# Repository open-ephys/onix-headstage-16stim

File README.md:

# ONIX 16-Channel Bidirectional Headstage
Serialized, multifunction headstage for wire electrode or silicon probe recordings.

- 16x bi-directional electrophysiology channels (±7V stimulus compliance)
- Integrated stimulus sequencer and memory
- Integrated real-time, room-scale 3D-position tracking
- Integrated absolute orientation tracking

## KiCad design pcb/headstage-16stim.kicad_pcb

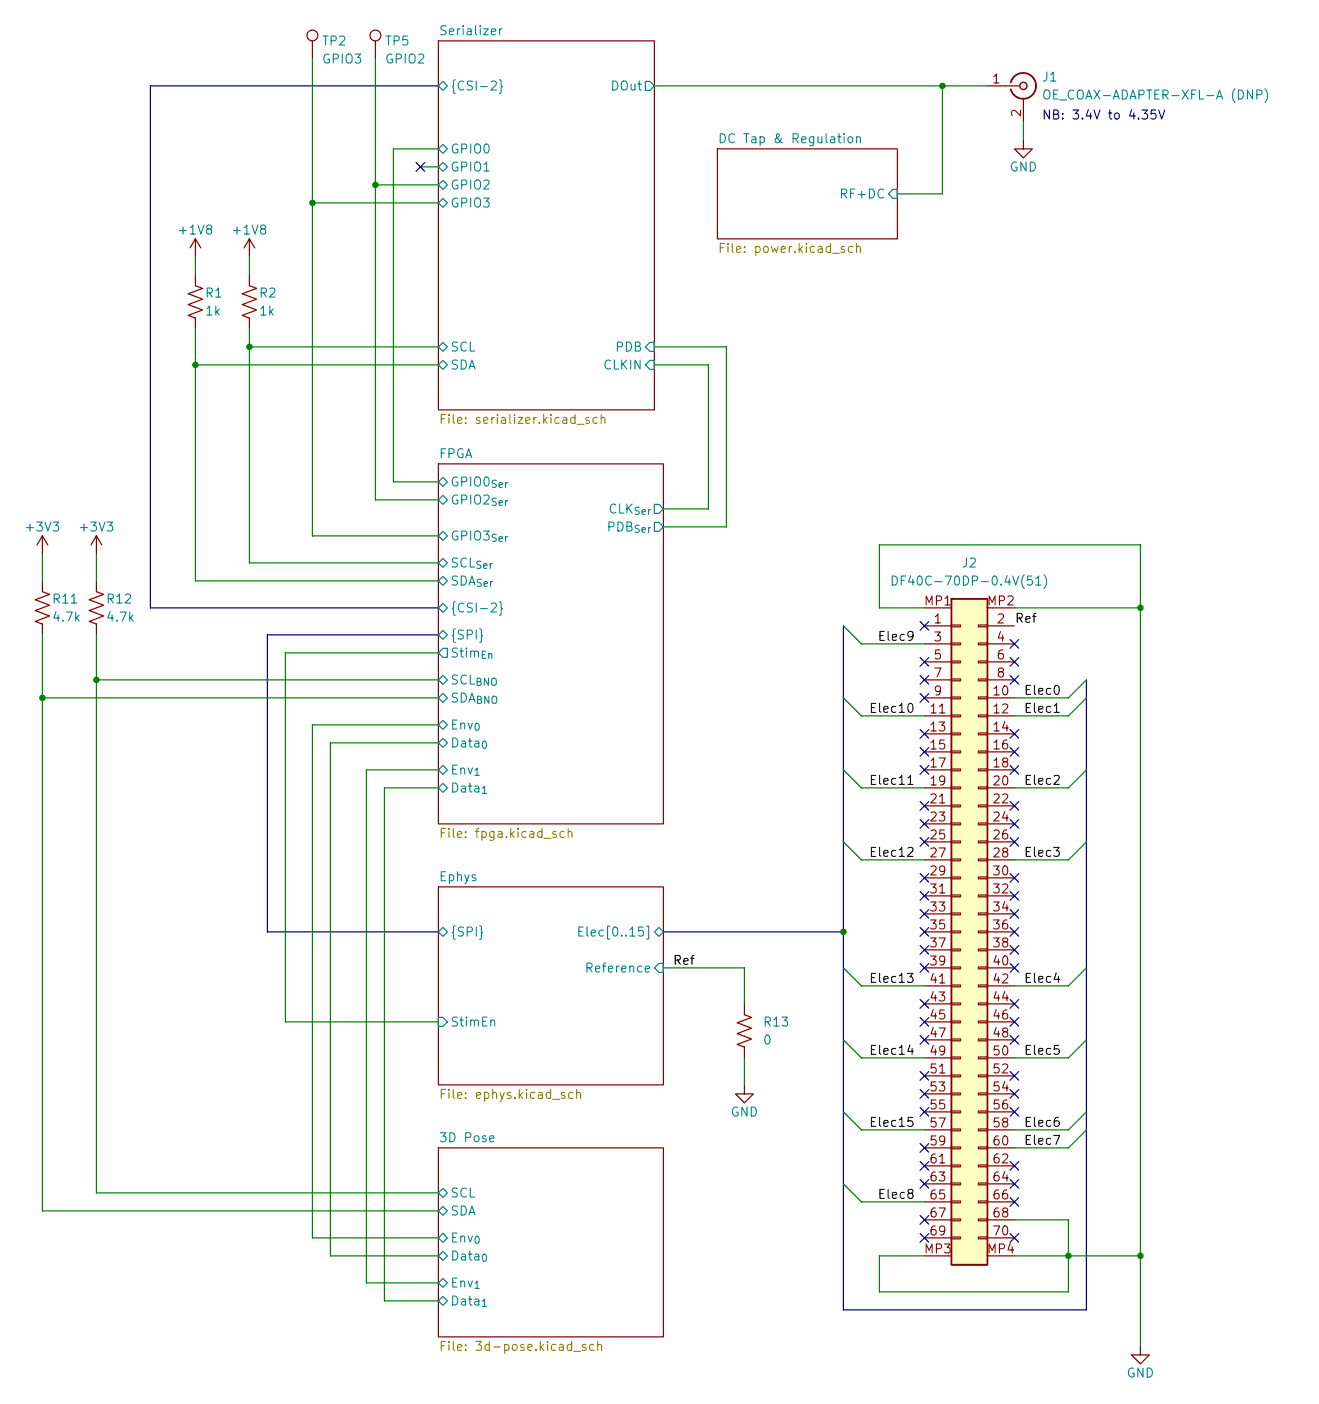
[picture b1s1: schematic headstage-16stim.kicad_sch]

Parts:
J1: OE_COAX-ADAPTER-XFL-A (DNP); OE_COAX-ADAPTER-XFL-A
J2: DF40C-70DP-0.4V(51); HIROSE_DF40C70DP04V51
R1, R2: 1k; R_0201_0603Metric
R11, R12: 4.7k; R_0201_0603Metric
R13: 0; R_0201_0603Metric
TP2: GPIO3; TestPoint_Pad_D0.6mm
TP5: GPIO2; TestPoint_Pad_D0.6mm

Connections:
+1V8: R1.1, R2.1; also elsewhere on the board
+3V3: R11.1, R12.1; also elsewhere on the board
/3D Pose/SCL: R12.2; also elsewhere on the board
/3D Pose/SDA: R11.2; also elsewhere on the board
/DC Tap & Regulation/RF+DC: J1.1 (In); also elsewhere on the board
/Ephys/Elec0: J2.10; also elsewhere on the board
/Ephys/Elec1: J2.12; also elsewhere on the board
/Ephys/Elec2: J2.20; also elsewhere on the board
/Ephys/Elec3: J2.28; also elsewhere on the board
/Ephys/Elec4: J2.42; also elsewhere on the board
/Ephys/Elec5: J2.50; also elsewhere on the board
/Ephys/Elec6: J2.58; also elsewhere on the board
/Ephys/Elec7: J2.60; also elsewhere on the board
/Ephys/Elec8: J2.65; also elsewhere on the board
/Ephys/Elec9: J2.3; also elsewhere on the board
/Ephys/Elec10: J2.11; also elsewhere on the board
/Ephys/Elec11: J2.19; also elsewhere on the board
/Ephys/Elec12: J2.27; also elsewhere on the board
/Ephys/Elec13: J2.41; also elsewhere on the board
/Ephys/Elec14: J2.49; also elsewhere on the board
/Ephys/Elec15: J2.57; also elsewhere on the board
/FPGA/GPIO2_{Ser}: TP5.1; also elsewhere on the board
/FPGA/GPIO3_{Ser}: TP2.1; also elsewhere on the board
/FPGA/SCL_{Ser}: R2.2; also elsewhere on the board
/FPGA/SDA_{Ser}: R1.2; also elsewhere on the board
/Ref: J2.2, R13.1; also elsewhere on the board
GND: J1.2 (Ext), J2.68, J2.MP1 (MountPin1), J2.MP2 (MountPin2), J2.MP3 (MountPin3), J2.MP4 (MountPin4), R13.2; also elsewhere on the board

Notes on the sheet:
NB: 3.4V to 4.35V

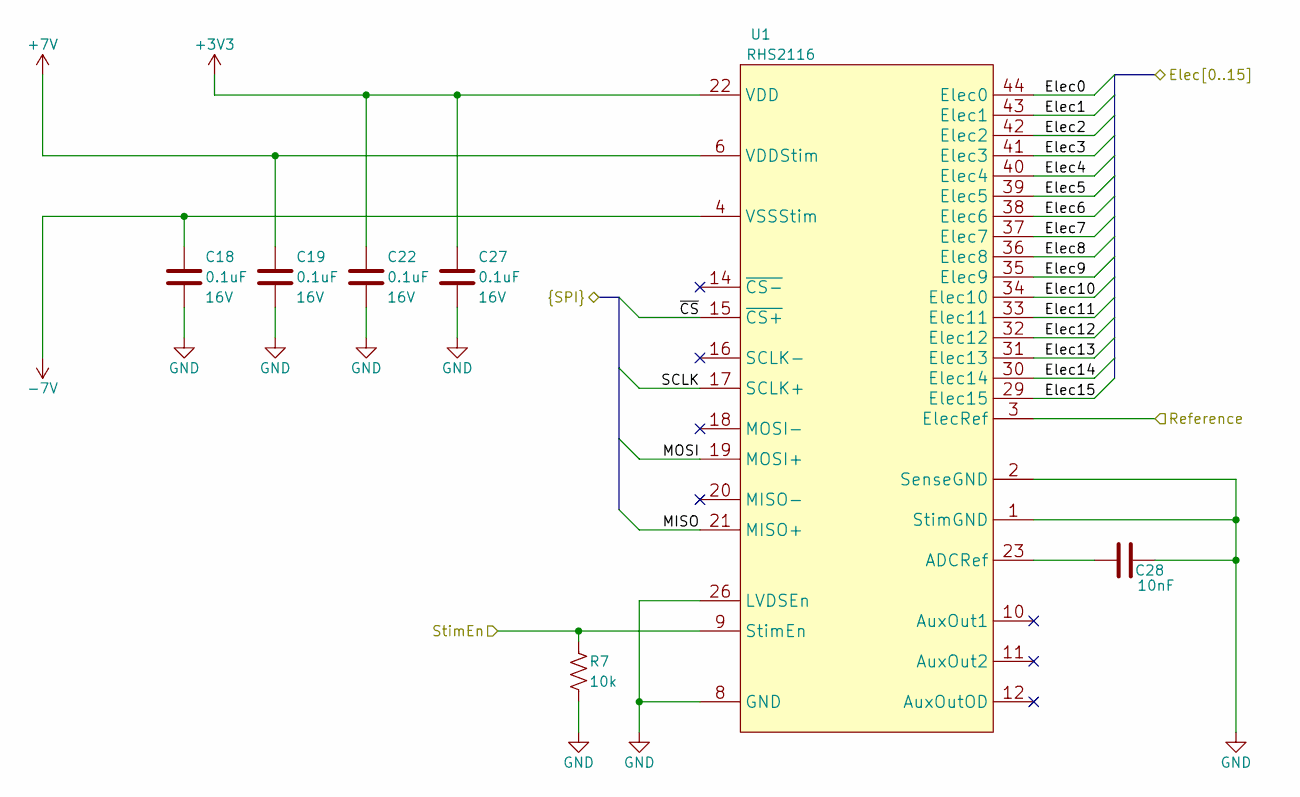
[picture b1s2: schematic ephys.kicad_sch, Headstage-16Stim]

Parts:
C18, C19, C22, C27: 0.1uF; C_0201_0603Metric; Voltage 16V
C28: 10nF; C_0201_0603Metric; Voltage 35V
R7: 10k; R_0201_0603Metric
U1: RHS2116; INTAN_QFN44-7.0x7.0x0.8_P0.5

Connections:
+3V3: C22.1, C27.1, U1.22 (VDD), U1.27 (VDD), U1.28 (VDD); also elsewhere on the board
+7V: C19.1, U1.6 (VDDStim), U1.7 (VDDStim); also elsewhere on the board
-7V: C18.1, U1.4 (VSSStim), U1.5 (VSSStim), U1.45 (VSSStim); also elsewhere on the board
/Ephys/Elec0: U1.44 (Elec0); also elsewhere on the board
/Ephys/Elec1: U1.43 (Elec1); also elsewhere on the board
/Ephys/Elec2: U1.42 (Elec2); also elsewhere on the board
/Ephys/Elec3: U1.41 (Elec3); also elsewhere on the board
/Ephys/Elec4: U1.40 (Elec4); also elsewhere on the board
/Ephys/Elec5: U1.39 (Elec5); also elsewhere on the board
/Ephys/Elec6: U1.38 (Elec6); also elsewhere on the board
/Ephys/Elec7: U1.37 (Elec7); also elsewhere on the board
/Ephys/Elec8: U1.36 (Elec8); also elsewhere on the board
/Ephys/Elec9: U1.35 (Elec9); also elsewhere on the board
/Ephys/Elec10: U1.34 (Elec10); also elsewhere on the board
/Ephys/Elec11: U1.33 (Elec11); also elsewhere on the board
/Ephys/Elec12: U1.32 (Elec12); also elsewhere on the board
/Ephys/Elec13: U1.31 (Elec13); also elsewhere on the board
/Ephys/Elec14: U1.30 (Elec14); also elsewhere on the board
/Ephys/Elec15: U1.29 (Elec15); also elsewhere on the board
/Ephys/MISO: U1.21 (MISO+); also elsewhere on the board
/Ephys/MOSI: U1.19 (MOSI+); also elsewhere on the board
/Ephys/SCLK: U1.17 (SCLK+); also elsewhere on the board
/Ephys/StimEn: R7.1, U1.9 (StimEn); also elsewhere on the board
/Ephys/~CS: U1.15 (~CS+); also elsewhere on the board
/Ref: U1.3 (ElecRef); also elsewhere on the board
GND: C18.2, C19.2, C22.2, C27.2, C28.2, R7.2, U1.1 (StimGND), U1.2 (SenseGND), U1.8 (GND), U1.13 (GND), U1.24 (GND), U1.25 (GND), U1.26 (LVDSEn); also elsewhere on the board
unnamed: C28.1, U1.23 (ADCRef)

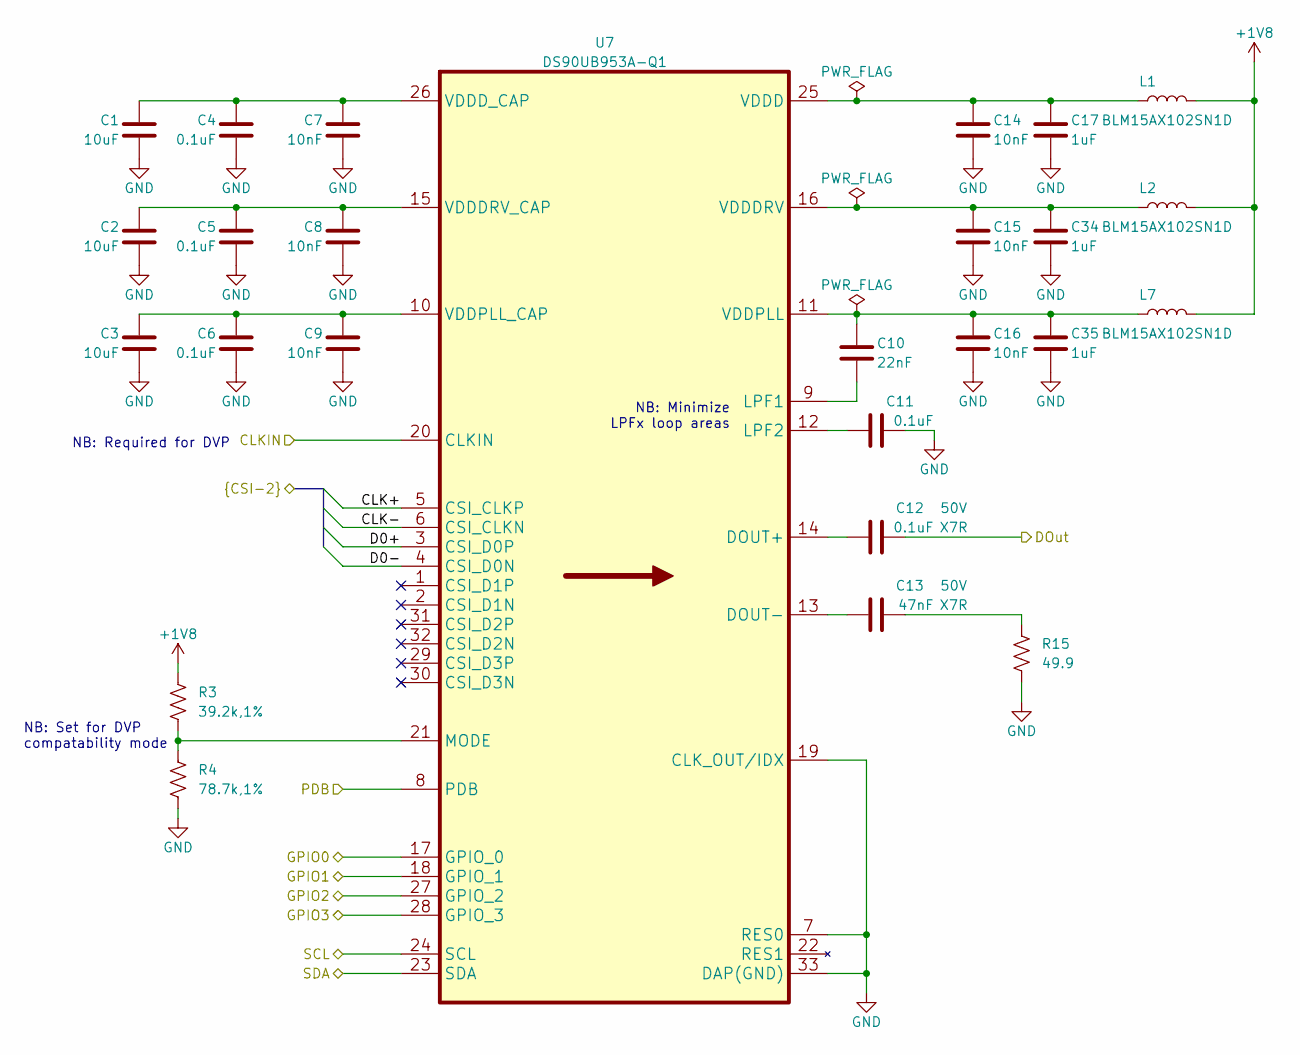
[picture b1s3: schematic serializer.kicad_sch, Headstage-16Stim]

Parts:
C1, C2, C3: 10uF; C_0402_1005Metric; Voltage 10V
C4, C5, C6, C11: 0.1uF; C_0201_0603Metric; Voltage 16V
C7, C8, C9, C14, C15, C16: 10nF; C_0201_0603Metric; Voltage 35V
C10: 22nF; C_0402_1005Metric; Voltage 35V
C12: 0.1uF; C_0402_1005Metric; Voltage 50V
C13: 47nF; C_0402_1005Metric; Voltage 50V
C17, C34, C35: 1uF; C_0402_1005Metric; Voltage 16V
L1, L2, L7: BLM15AX102SN1D; L_0402_1005Metric
R3: 39.2k,1%; R_0201_0603Metric
R4: 78.7k,1%; R_0201_0603Metric
R15: 49.9; R_0201_0603Metric
U7: DS90UB953A-Q1; TI_RHB0032P

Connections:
+1V8: L1.2, L2.2, L7.2, R3.1; also elsewhere on the board
/DC Tap & Regulation/RF+DC: C12.2; also elsewhere on the board
/FPGA/CLK+: U7.5 (CSI_CLKP); also elsewhere on the board
/FPGA/CLK-: U7.6 (CSI_CLKN); also elsewhere on the board
/FPGA/CLK_{Ser}: U7.20 (CLKIN); also elsewhere on the board
/FPGA/D0+: U7.3 (CSI_D0P); also elsewhere on the board
/FPGA/D0-: U7.4 (CSI_D0N); also elsewhere on the board
/FPGA/GPIO0_{Ser}: U7.17 (GPIO_0); also elsewhere on the board
/FPGA/GPIO2_{Ser}: U7.27 (GPIO_2); also elsewhere on the board
/FPGA/GPIO3_{Ser}: U7.28 (GPIO_3); also elsewhere on the board
/FPGA/PDB_{Ser}: U7.8 (PDB); also elsewhere on the board
/FPGA/SCL_{Ser}: U7.24 (SCL); also elsewhere on the board
/FPGA/SDA_{Ser}: U7.23 (SDA); also elsewhere on the board
/Serializer/GPIO1: U7.18 (GPIO_1)
GND: C1.2, C2.2, C3.2, C4.2, C5.2, C6.2, C7.2, C8.2, C9.2, C11.2, C14.2, C15.2, C16.2, C17.2, C34.2, C35.2, R4.2, R15.2, U7.7 (RES0), U7.19 (CLK_OUT/IDX), U7.33 (DAP(GND)); also elsewhere on the board
unnamed: C13.2, R15.1
unnamed: C12.1, U7.14 (DOUT+)
unnamed: C13.1, U7.13 (DOUT-)
unnamed: C10.2, U7.9 (LPF1)
unnamed: C11.1, U7.12 (LPF2)
unnamed: R3.2, R4.1, U7.21 (MODE)
unnamed: C14.1, C17.1, L1.1, U7.25 (VDDD)
unnamed: C15.1, C34.1, L2.1, U7.16 (VDDDRV)
unnamed: C2.1, C5.1, C8.1, U7.15 (VDDDRV_CAP)
unnamed: C1.1, C4.1, C7.1, U7.26 (VDDD_CAP)
unnamed: C10.1, C16.1, C35.1, L7.1, U7.11 (VDDPLL)
unnamed: C3.1, C6.1, C9.1, U7.10 (VDDPLL_CAP)

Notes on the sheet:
NB: Set for DVP compatability mode
NB: Required for DVP
NB: Minimize LPFx loop areas

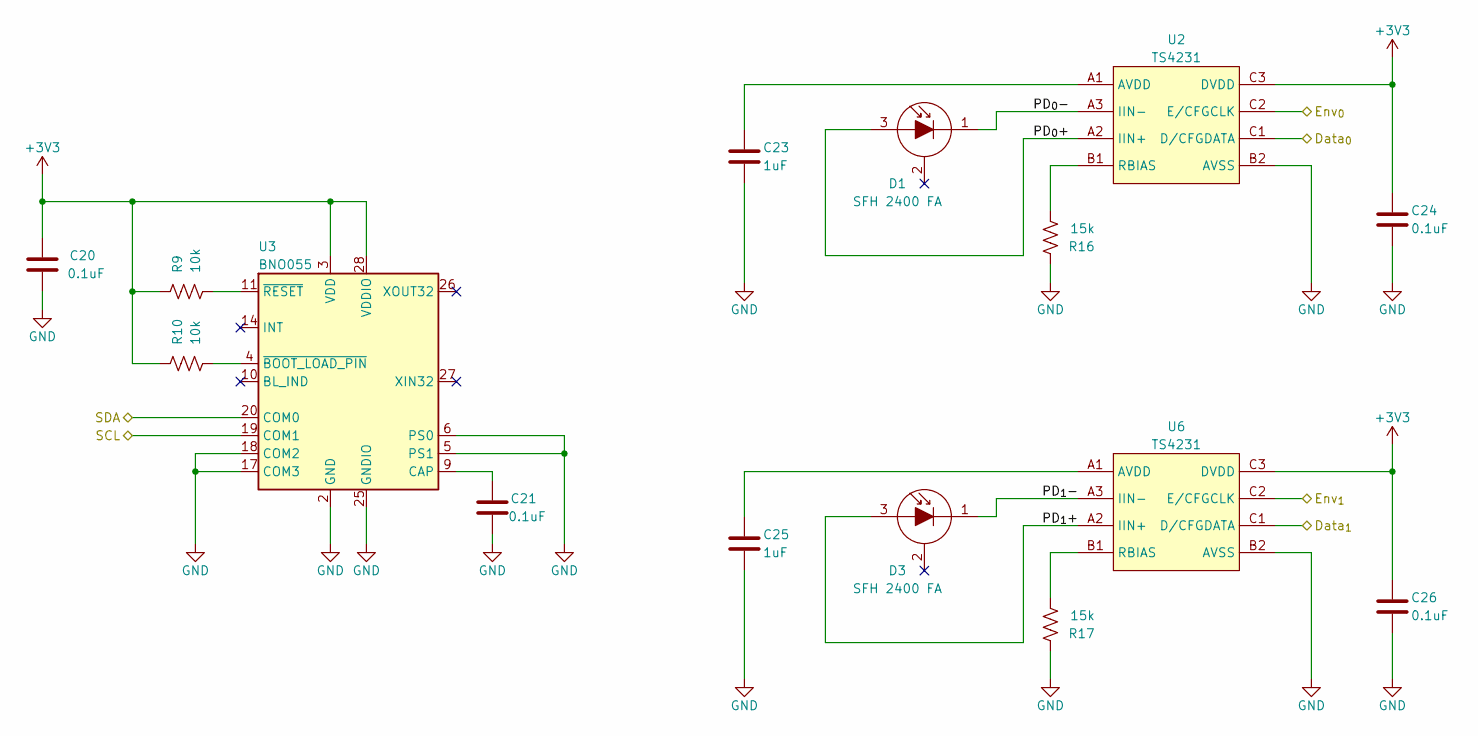
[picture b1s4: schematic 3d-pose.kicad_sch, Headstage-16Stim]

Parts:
C20, C21, C24, C26: 0.1uF; C_0201_0603Metric; Voltage 16V
C23, C25: 1uF; C_0402_1005Metric; Voltage 16V
D1, D3: SFH 2400 FA; OSRAM_SFH2400FA-Tight
R9, R10: 10k; R_0201_0603Metric
R16, R17: 15k; R_0201_0603Metric
U2, U6: TS4231; TRIAD_BGA-9_3x3_1.7x1.7mm
U3: BNO055; LGA-28_5.2x3.8mm_P0.5mm

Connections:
+3V3: C20.2, C24.2, C26.2, R9.1, R10.1, U2.C3 (DVDD), U3.3 (VDD), U3.28 (VDDIO), U6.C3 (DVDD); also elsewhere on the board
/3D Pose/Data_{0}: U2.C1 (D/CFGDATA); also elsewhere on the board
/3D Pose/Data_{1}: U6.C1 (D/CFGDATA); also elsewhere on the board
/3D Pose/Env_{0}: U2.C2 (E/CFGCLK); also elsewhere on the board
/3D Pose/Env_{1}: U6.C2 (E/CFGCLK); also elsewhere on the board
/3D Pose/PD_{0}+: D1.3 (A), U2.A2 (IIN+)
/3D Pose/PD_{0}-: D1.1 (K), U2.A3 (IIN-)
/3D Pose/PD_{1}+: D3.3 (A), U6.A2 (IIN+)
/3D Pose/PD_{1}-: D3.1 (K), U6.A3 (IIN-)
/3D Pose/SCL: U3.19 (COM1); also elsewhere on the board
/3D Pose/SDA: U3.20 (COM0); also elsewhere on the board
GND: C20.1, C21.1, C23.2, C24.1, C25.2, C26.1, R16.1, R17.1, U2.B2 (AVSS), U2.B3 (AVSS), U3.2 (GND), U3.5 (PS1), U3.6 (PS0), U3.15 (GNDIO), U3.16 (GNDIO), U3.17 (COM3), U3.18 (COM2), U3.25 (GNDIO), U6.B2 (AVSS), U6.B3 (AVSS); also elsewhere on the board
unnamed: C23.1, U2.A1 (AVDD)
unnamed: R16.2, U2.B1 (RBIAS)
unnamed: C21.2, U3.9 (CAP)
unnamed: R10.2, U3.4 (~BOOT_LOAD_PIN)
unnamed: R9.2, U3.11 (~RESET)
unnamed: C25.1, U6.A1 (AVDD)
unnamed: R17.2, U6.B1 (RBIAS)

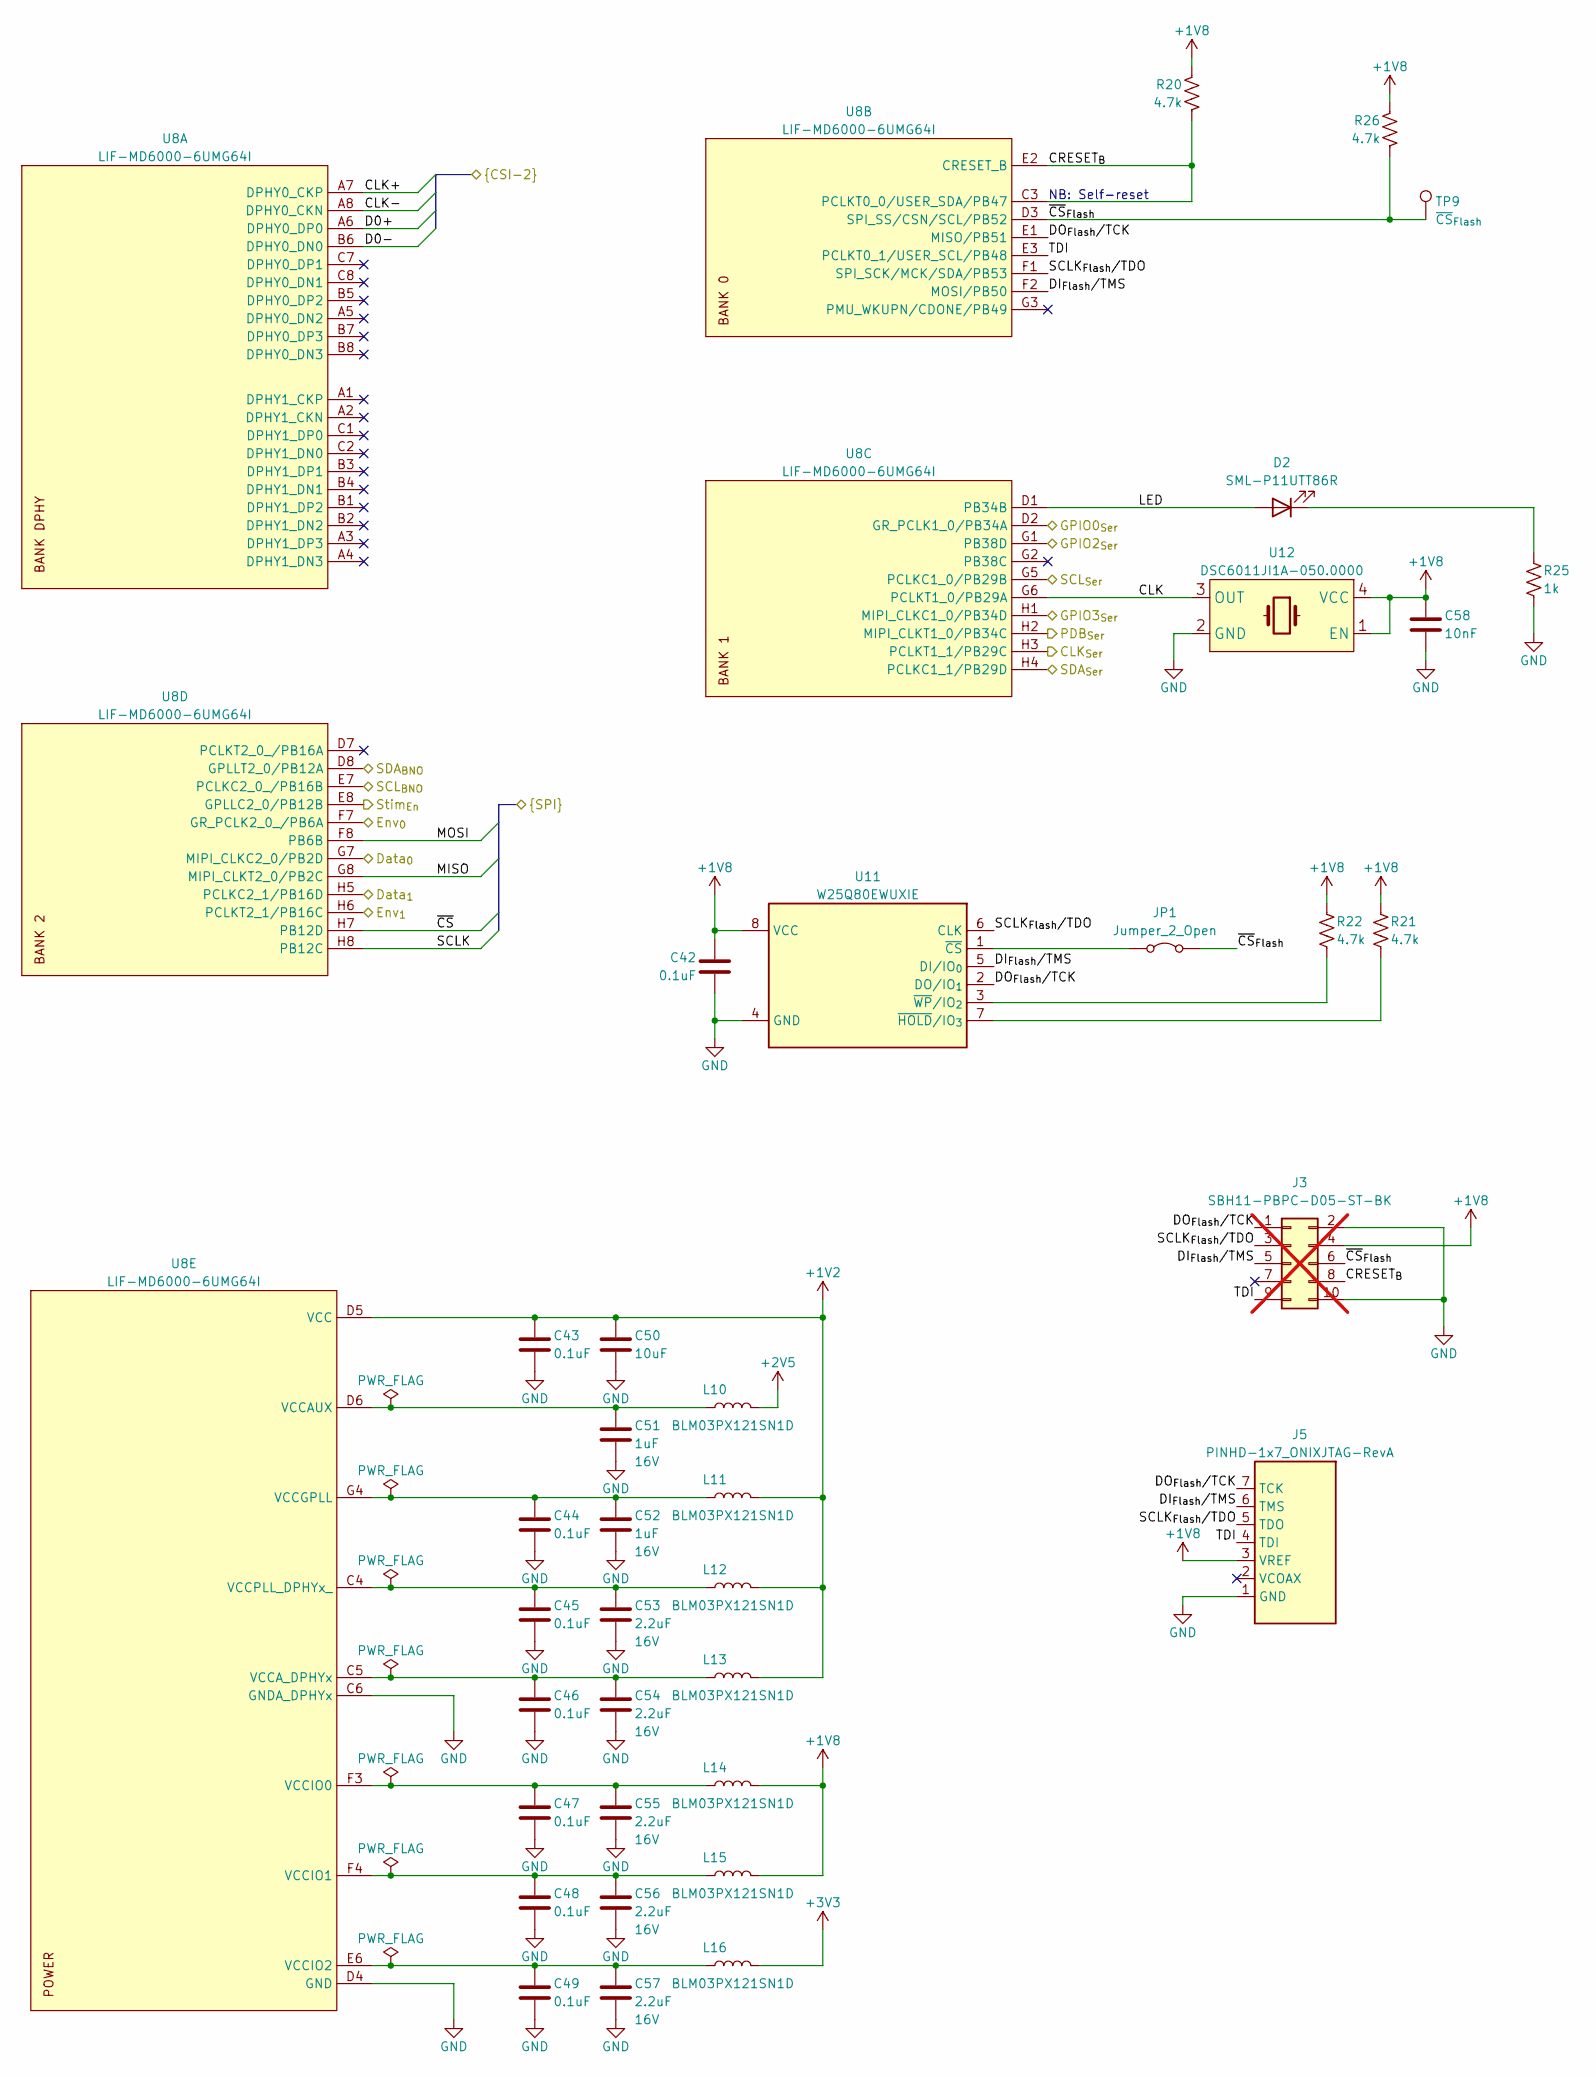
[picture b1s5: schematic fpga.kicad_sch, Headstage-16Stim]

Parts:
C42, C43, C44, C45, C46, C47, C48, C49: 0.1uF; C_0201_0603Metric; Voltage 16V
C50: 10uF; C_0402_1005Metric; Voltage 10V
C51, C52: 1uF; C_0402_1005Metric; Voltage 16V
C53, C54, C55, C56, C57: 2.2uF; C_0402_1005Metric; Voltage 16V
C58: 10nF; C_0201_0603Metric; Voltage 35V
D2: SML-P11UTT86R; ROHM_SML-P11MTT86R
J3: SBH11-PBPC-D05-ST-BK; IDC-Header_2x05_P2.54mm_Vertical; not fitted
J5: PINHD-1x7_ONIXJTAG-RevA; ONIXJTAG-RevA
JP1: Jumper_2_Open; OE_SolderJumper-2_0201_Open_Pad
L10, L11, L12, L13, L14, L15, L16: BLM03PX121SN1D; L_0201_0603Metric
R20, R21, R22, R26: 4.7k; R_0201_0603Metric
R25: 1k; R_0201_0603Metric
TP9: ~{CS}_{Flash}; TestPoint_Pad_D0.6mm
U8: LIF-MD6000-6UMG64I; LATTICE_ufcBGA64C40P8X8_3.5X3.5X1.0
U11: W25Q80EWUXIE; WINBOND_USON8-2x3x0.6
U12: DSC6011JI1A-050.0000; MICROCHIP_VFLGA4-2.0x1.6

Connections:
+1V2: C43.1, C50.1, L11.2, L12.2, L13.2, U8.D5 (VCC), U8.E4 (VCC); also elsewhere on the board
+1V8: C42.1, C58.1, J3.4, J5.3 (VREF), L14.2, L15.2, R20.1, R21.1, R22.1, R26.1, U11.8 (VCC), U12.1 (EN), U12.4 (VCC); also elsewhere on the board
+2V5: L10.2; also elsewhere on the board
+3V3: L16.2; also elsewhere on the board
/3D Pose/Data_{0}: U8.G7 (MIPI_CLKC2_0/PB2D); also elsewhere on the board
/3D Pose/Data_{1}: U8.H5 (PCLKC2_1/PB16D); also elsewhere on the board
/3D Pose/Env_{0}: U8.F7 (GR_PCLK2_0_/PB6A); also elsewhere on the board
/3D Pose/Env_{1}: U8.H6 (PCLKT2_1/PB16C); also elsewhere on the board
/3D Pose/SCL: U8.E7 (PCLKC2_0_/PB16B); also elsewhere on the board
/3D Pose/SDA: U8.D8 (GPLLT2_0/PB12A); also elsewhere on the board
/Ephys/MISO: U8.G8 (MIPI_CLKT2_0/PB2C); also elsewhere on the board
/Ephys/MOSI: U8.F8 (PB6B); also elsewhere on the board
/Ephys/SCLK: U8.H8 (PB12C); also elsewhere on the board
/Ephys/StimEn: U8.E8 (GPLLC2_0/PB12B); also elsewhere on the board
/Ephys/~CS: U8.H7 (PB12D); also elsewhere on the board
/FPGA/CLK: U8.G6 (PCLKT1_0/PB29A), U12.3 (OUT)
/FPGA/CLK+: U8.A7 (DPHY0_CKP); also elsewhere on the board
/FPGA/CLK-: U8.A8 (DPHY0_CKN); also elsewhere on the board
/FPGA/CLK_{Ser}: U8.H3 (PCLKT1_1/PB29C); also elsewhere on the board
/FPGA/CRESET_{B}: J3.8, R20.2, U8.C3 (PCLKT0_0/USER_SDA/PB47), U8.E2 (CRESET_B)
/FPGA/D0+: U8.A6 (DPHY0_DP0); also elsewhere on the board
/FPGA/D0-: U8.B6 (DPHY0_DN0); also elsewhere on the board
/FPGA/DI_{Flash}/TMS: J3.5, J5.6 (TMS), U8.F2 (MOSI/PB50), U11.5 (DI/IO_{0})
/FPGA/DO_{Flash}/TCK: J3.1, J5.7 (TCK), U8.E1 (MISO/PB51), U11.2 (DO/IO_{1})
/FPGA/GPIO0_{Ser}: U8.D2 (GR_PCLK1_0/PB34A); also elsewhere on the board
/FPGA/GPIO2_{Ser}: U8.G1 (PB38D); also elsewhere on the board
/FPGA/GPIO3_{Ser}: U8.H1 (MIPI_CLKC1_0/PB34D); also elsewhere on the board
/FPGA/LED: D2.2 (A), U8.D1 (PB34B)
/FPGA/PDB_{Ser}: U8.H2 (MIPI_CLKT1_0/PB34C); also elsewhere on the board
/FPGA/SCLK_{Flash}/TDO: J3.3, J5.5 (TDO), U8.F1 (SPI_SCK/MCK/SDA/PB53), U11.6 (CLK)
/FPGA/SCL_{Ser}: U8.G5 (PCLKC1_0/PB29B); also elsewhere on the board
/FPGA/SDA_{Ser}: U8.H4 (PCLKC1_1/PB29D); also elsewhere on the board
/FPGA/TDI: J3.9, J5.4 (TDI), U8.E3 (PCLKT0_1/USER_SCL/PB48)
/FPGA/~CS_{Flash}: J3.6, JP1.2 (B), R26.2, TP9.1, U8.D3 (SPI_SS/CSN/SCL/PB52)
GND: C42.2, C43.2, C44.2, C45.2, C46.2, C47.2, C48.2, C49.2, C50.2, C51.2, C52.2, C53.2, C54.2, C55.2, C56.2, C57.2, C58.2, J3.2, J3.10, J5.1 (GND), R25.2, U8.C6 (GNDA_DPHYx), U8.D4 (GND), U8.E5 (GND), U8.F5 (GND), U11.4 (GND), U11.9 (GND), U12.2 (GND); also elsewhere on the board
unnamed: C49.1, C57.1, L16.1, U8.E6 (VCCIO2), U8.F6 (VCCIO2)
unnamed: D2.1 (K), R25.1
unnamed: JP1.1 (A), U11.1 (~CS)
unnamed: C51.1, L10.1, U8.D6 (VCCAUX)
unnamed: C46.1, C54.1, L13.1, U8.C5 (VCCA_DPHYx)
unnamed: C44.1, C52.1, L11.1, U8.G4 (VCCGPLL)
unnamed: C47.1, C55.1, L14.1, U8.F3 (VCCIO0)
unnamed: C48.1, C56.1, L15.1, U8.F4 (VCCIO1)
unnamed: C45.1, C53.1, L12.1, U8.C4 (VCCPLL_DPHYx_)
unnamed: R21.2, U11.7 (~HOLD/IO_{3})
unnamed: R22.2, U11.3 (~WP/IO_{2})

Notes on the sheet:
NB: Self-reset

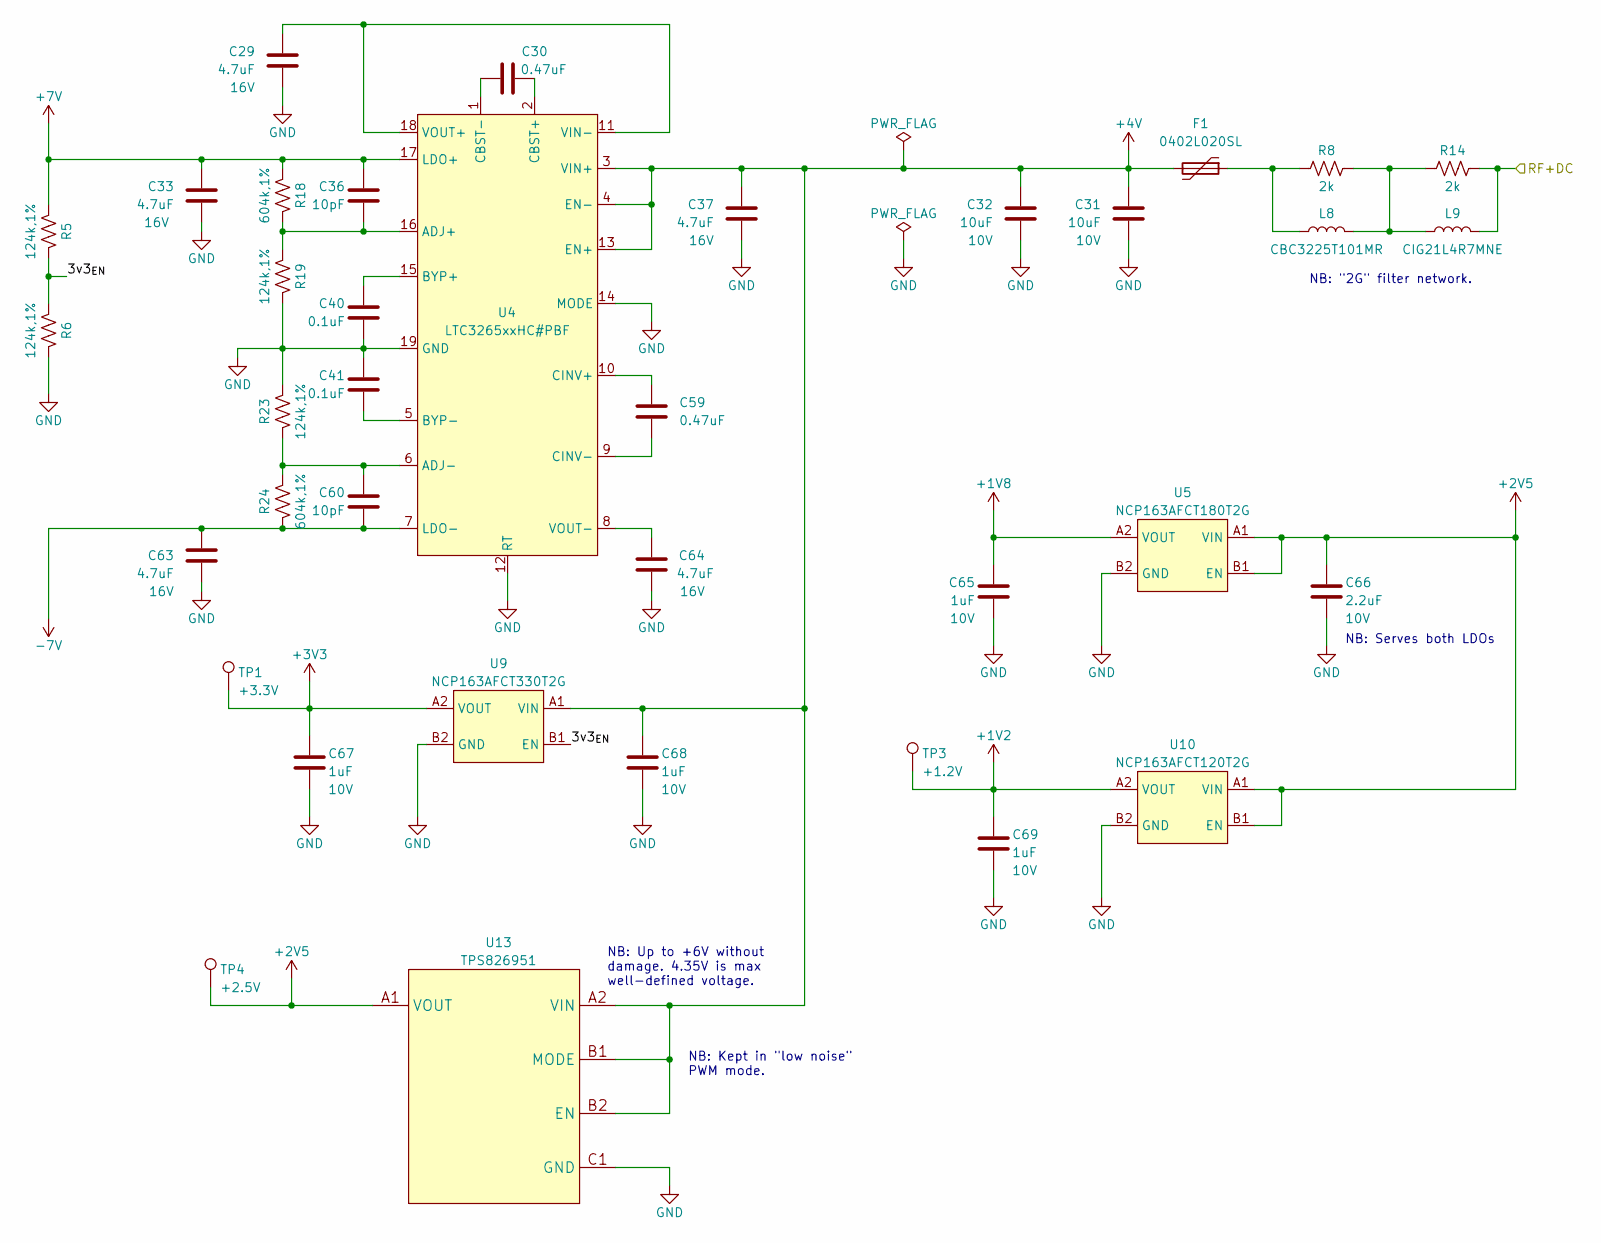
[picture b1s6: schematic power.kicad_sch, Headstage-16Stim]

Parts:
C29, C33, C37, C63, C64: 4.7uF; C_0402_1005Metric; Voltage 16V
C30, C59: 0.47uF; C_0402_1005Metric; Voltage 35V
C31, C32: 10uF; C_0402_1005Metric; Voltage 10V
C36, C60: 10pF; C_0201_0603Metric; Voltage 50V
C40, C41: 0.1uF; C_0201_0603Metric; Voltage 16V
C65, C67, C68, C69: 1uF; C_0201_0603Metric; Voltage 10V
C66: 2.2uF; C_0201_0603Metric; Voltage 10V
F1: 0402L020SL; LITTLEFUSE_0402
L8: CBC3225T101MR; L_1210_3225Metric
L9: CIG21L4R7MNE; L_0805_2012Metric
R5, R6, R19, R23: 124k,1%; R_0201_0603Metric
R8, R14: 2k; R_0201_0603Metric
R18, R24: 604k,1%; R_0201_0603Metric
TP1: +3.3V; TestPoint_Pad_D0.6mm
TP3: +1.2V; TestPoint_Pad_D0.6mm
TP4: +2.5V; TestPoint_Pad_D0.6mm
U4: LTC3265xxHC#PBF; LINEAR_SON50P300X500X80-19N-D
U5: NCP163AFCT180T2G; ONSEMI_567JZ_WLCSP4-0.64x0.64
U9: NCP163AFCT330T2G; ONSEMI_567JZ_WLCSP4-0.64x0.64
U10: NCP163AFCT120T2G; ONSEMI_567JZ_WLCSP4-0.64x0.64
U13: TPS826951; TI_SIP0008B

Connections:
+1V2: C69.1, TP3.1, U10.A2 (VOUT); also elsewhere on the board
+1V8: C65.1, U5.A2 (VOUT); also elsewhere on the board
+2V5: C66.1, TP4.1, U5.A1 (VIN), U5.B1 (EN), U10.A1 (VIN), U10.B1 (EN), U13.A1 (VOUT); also elsewhere on the board
+3V3: C67.1, TP1.1, U9.A2 (VOUT); also elsewhere on the board
+4V: C31.2, C32.2, C37.2, C68.1, F1.2, U4.3 (VIN+), U4.4 (EN-), U4.13 (EN+), U9.A1 (VIN), U13.A2 (VIN), U13.A3 (VIN), U13.B1 (MODE), U13.B2 (EN)
+7V: C33.2, C36.1, R5.2, R18.2, U4.17 (LDO+); also elsewhere on the board
-7V: C60.2, C63.2, R24.2, U4.7 (LDO-); also elsewhere on the board
/DC Tap & Regulation/3v3_{EN}: R5.1, R6.2, U9.B1 (EN)
/DC Tap & Regulation/RF+DC: L9.1, R14.2; also elsewhere on the board
GND: C29.1, C31.1, C32.1, C33.1, C37.1, C40.2, C41.1, C63.1, C64.1, C65.2, C66.2, C67.2, C68.2, C69.2, R6.1, R19.1, R23.1, U4.12 (RT), U4.14 (MODE), U4.19 (GND), U5.B2 (GND), U9.B2 (GND), U10.B2 (GND), U13.C1 (GND), U13.C2 (GND), U13.C3 (GND); also elsewhere on the board
unnamed: F1.1, L8.1, R8.1
unnamed: L8.2, L9.2, R8.2, R14.1
unnamed: C36.2, R18.1, R19.2, U4.16 (ADJ+)
unnamed: C60.1, R23.2, R24.1, U4.6 (ADJ-)
unnamed: C40.1, U4.15 (BYP+)
unnamed: C41.2, U4.5 (BYP-)
unnamed: C30.1, U4.2 (CBST+)
unnamed: C30.2, U4.1 (CBST-)
unnamed: C59.2, U4.10 (CINV+)
unnamed: C59.1, U4.9 (CINV-)
unnamed: C29.2, U4.11 (VIN-), U4.18 (VOUT+)
unnamed: C64.2, U4.8 (VOUT-)

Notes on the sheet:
NB: Up to +6V without damage. 4.35V is max well-defined voltage.
NB: "2G" filter network.
NB: Serves both LDOs
NB: Kept in "low noise" PWM mode.

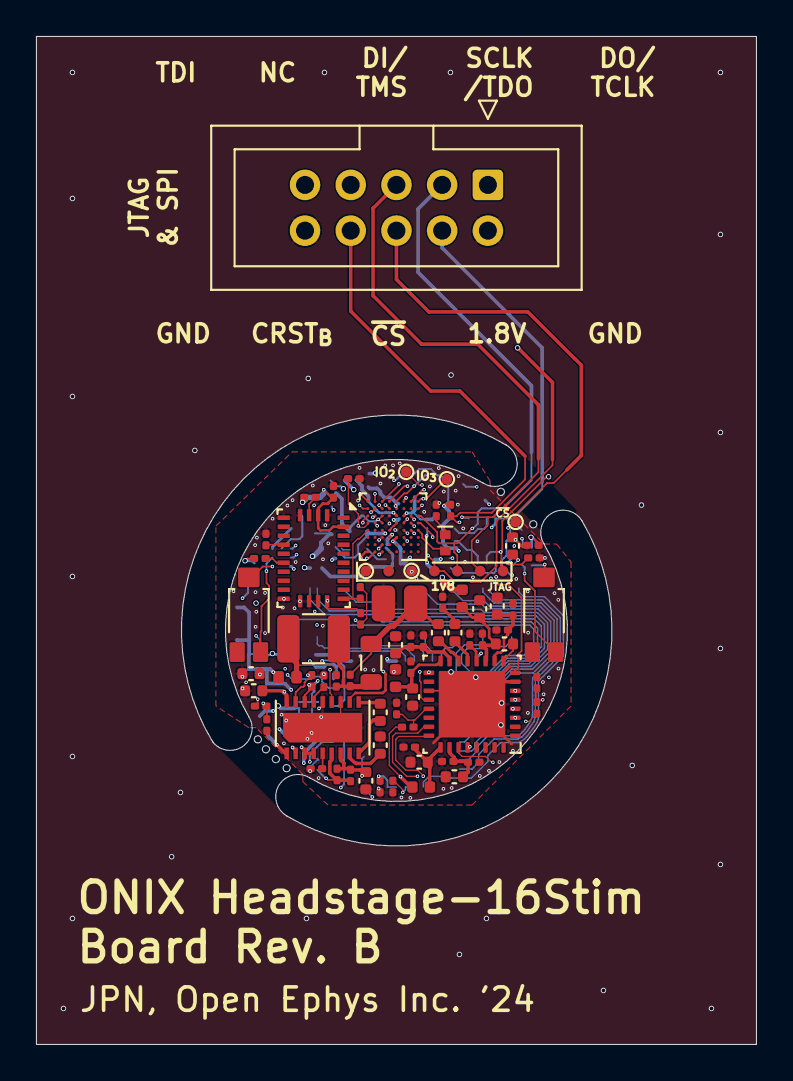
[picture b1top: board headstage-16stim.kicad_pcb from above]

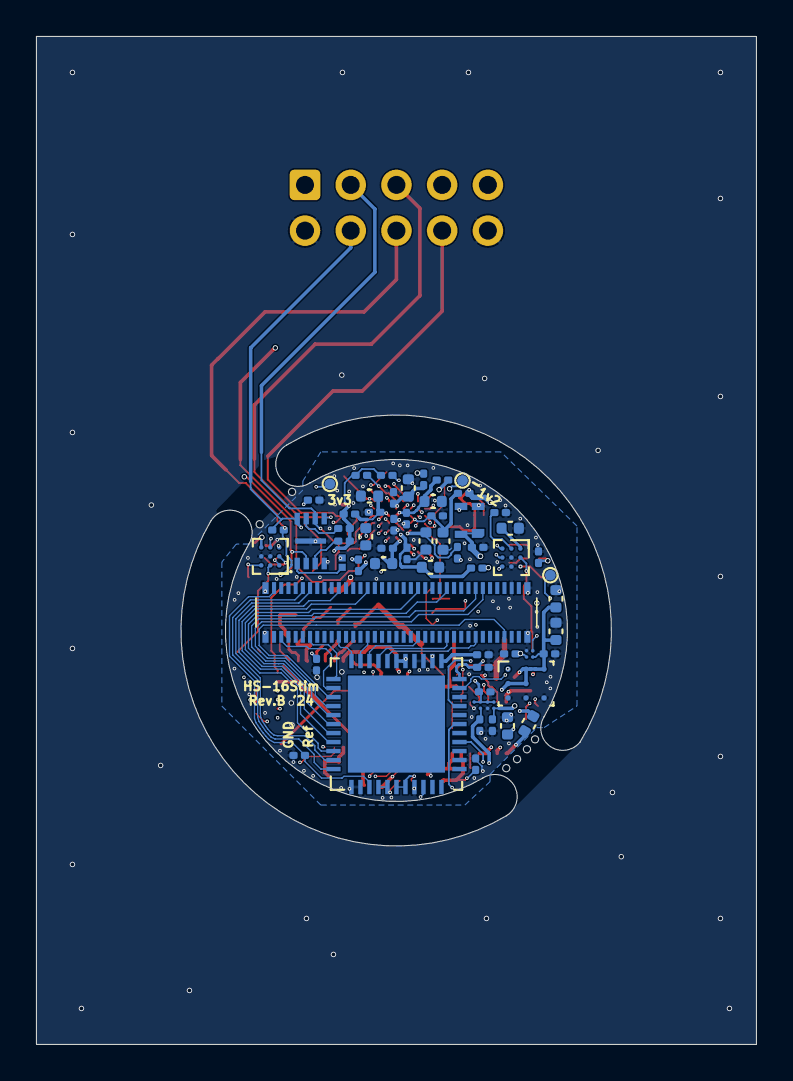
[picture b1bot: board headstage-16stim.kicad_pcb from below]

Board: 6 copper layers, 40.0 x 56.0 mm, 131 parts (60 on the bottom side), 104 nets.

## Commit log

2022-12-05 Initial commit
    - Sending to speedy for quote and iteration
2022-12-05 Move BOM folder to manufacturing folder
    - Remove redundant gerber PNP files and replace with CSVs
    - Update html BOM to include TempCo
2023-01-05 PCB Revision A
    - Added production files from Speedy
2024-10-01 Revision B
    - Bring in changes from headstage-rhs116 rev. C that should make this design
    fully functional
